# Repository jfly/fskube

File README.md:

fskube 
======

A software modem with a web audio api demo.

* `make` builds the c++ code with clang++. `CXX=g++ make -e` to build with g++.
* `make js` builds fskube.js. Requires emscripten.
* `make jsmin` compresses fskube.js to fskube.min.js. Requires clojure compiler.
* `make check` runs the tests. Requires swig to produce the python wrapper for the c++ code.

* `make serve` starts up a local server

## TODO

* Move off gh-pages branch
* Add android to travis-ci
* Integrate android release with git tags

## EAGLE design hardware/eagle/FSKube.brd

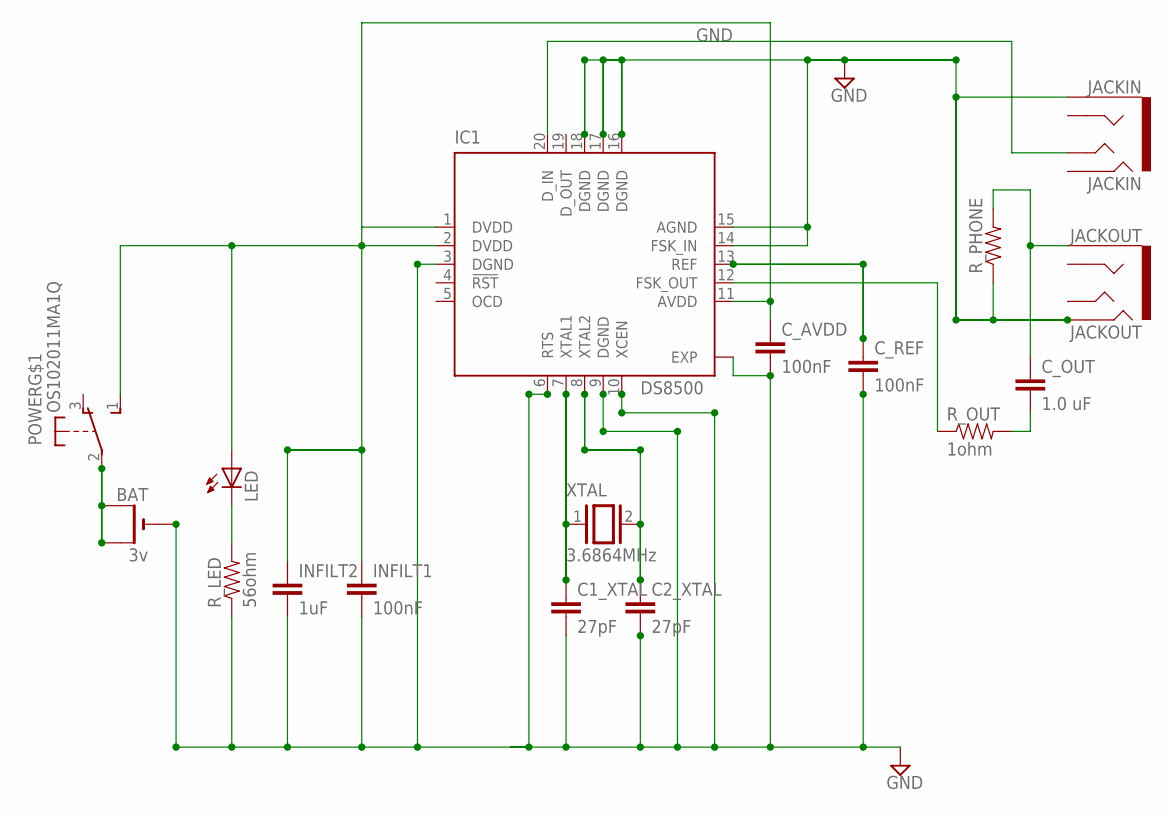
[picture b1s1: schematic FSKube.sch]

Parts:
BAT: 3v; CR1220-THM
C1_XTAL, C2_XTAL: 27pF; C2.5-2
C_AVDD: 100nF; C2.5-2
C_OUT: 1.0 uF; C2.5-2
C_REF: 100nF; C2.5-2
IC1: DS8500; TQFN20-5X5
INFILT1: 100nF; C2.5-2
INFILT2: 1uF; C2.5-2
JACKIN: JACKIN; AUDIO-JACK-TRRS-SMD
JACKOUT: JACKOUT; AUDIO-JACK-TRRS-SMD
LED: LED3MM
POWER: OS102011MA1Q
R_LED: 56ohm; 1/6W-RES
R_OUT: 1ohm; 1/6W-RES
R_PHONE: RESISTORPTH-1/6W; 1/6W-RES
XTAL: 3.6864MHz; QS

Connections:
GND: BAT.-, C1_XTAL.2, C2_XTAL.2, C_AVDD.2, C_REF.2, IC1.3 (DGND), IC1.6 (RTS), IC1.9 (DGND), IC1.10 (XCEN), IC1.14 (FSK_IN), IC1.15 (AGND), IC1.16 (DGND), IC1.17 (DGND), IC1.18 (DGND), IC1.EXP, INFILT1.2, INFILT2.2, JACKIN.EARTH, JACKOUT.RING2, R_LED.1, R_PHONE.1
unnamed: C1_XTAL.1, IC1.7 (XTAL1), XTAL.1
unnamed: C2_XTAL.1, IC1.8 (XTAL2), XTAL.2
unnamed: LED.K (C), R_LED.2
unnamed: IC1.20 (D_IN), JACKIN.TIP
unnamed: BAT.+1 (+), BAT.+2 (+1), POWER.2
unnamed: IC1.12 (FSK_OUT), R_OUT.1
unnamed: C_REF.1, IC1.13 (REF)
unnamed: C_OUT.2, R_OUT.2
unnamed: C_OUT.1, JACKOUT.EARTH, R_PHONE.2
VDD: C_AVDD.1, IC1.1 (DVDD), IC1.2 (DVDD), IC1.11 (AVDD), INFILT1.1, INFILT2.1, LED.A, POWER.1 (S)

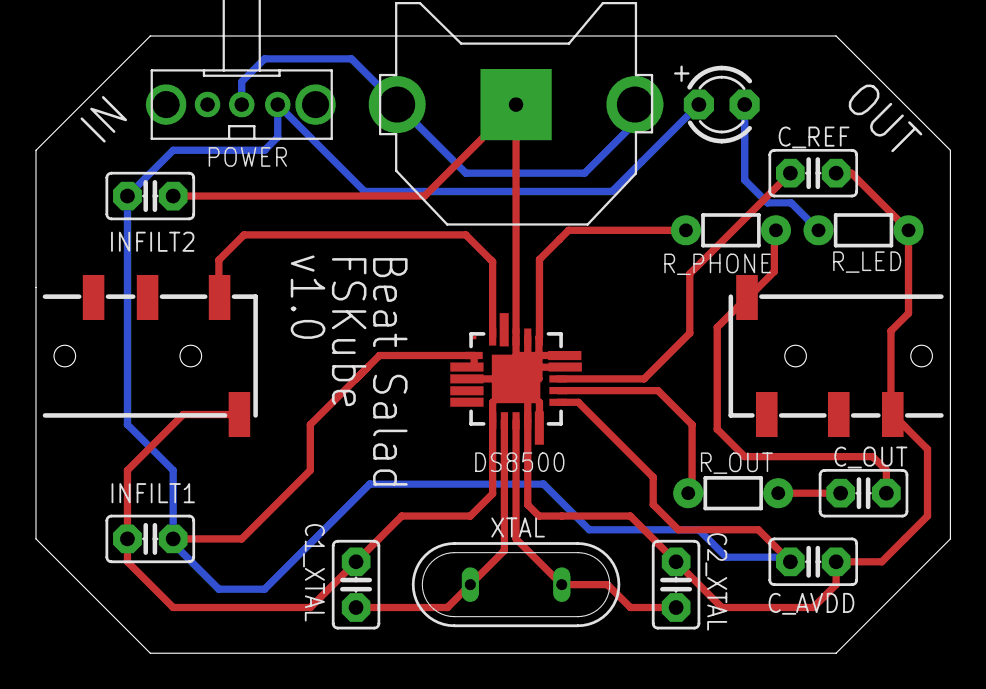
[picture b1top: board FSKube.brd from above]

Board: 2 copper layers, 50.8 x 34.3 mm, 17 parts (0 on the bottom side), 11 nets.

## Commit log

2014-03-09 EVERYTHING. It works, mostly!
2014-03-09 Updated README.
2014-03-09 Shuffled some variables around, increased buffer size so demo works on my Nexus 5.
2014-03-24 Parsing 1200/2200 hz fsk! Seems to work fine.
2014-03-24 Added support for continuous phase fsk-ing. Demodulating doesn't always work =(
2014-05-05 Ported to c++! emscripten and swing, oh my! The current makefile works, but hopefully could be cleaned up.
2014-05-05 Some Makefile cleanup.
2014-05-05 Moved code into a src/ directory. Updated Makefile to generate stuff in the bld/ directory.
2014-05-05 Yayy python unittest!
2014-05-05 ModemRoundtripTest.py now fails =(. I'm pretty sure we have this same bug in the original javascript code, so nothing to worry about =).
2014-05-07 Using emscripten's embind to expose our c++ api to javascript. Unfortunately, embind seems to not support multiple inheritance, so I had to change Sender to be a subclass of Receiver, which seems rea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
2014-05-10 Updated README and Makefile to explain all the different targets we have.
2014-05-10 Ported main.js to use fskube.js! Unfortunately, looks like it's buggy =(.
2014-05-12 Tweaked test to be more python when converting bool to int.
2014-05-12 Now ignoring all text except for "0" and "1" in textboxes.
2014-05-14 Ported example to use c++ modulator/demodulator! Also ported modemtest.js to ModemRoundtripTest.py.
2014-05-14 CLUTTERING HISTORY WITH COMPILED CODE
2014-05-14 fueling my ocd
2014-05-16 Tweaked html demo to use 1200hz and 2200hz, by adding a disgusting amount of padding to our signal.
2014-05-19 Added Rs232or and DeRs232or. Updated index.html to use it! Shuffled test code around a bit.
2014-05-19 Back to using fastcomp!
2014-05-22 Added StackmatSynthesizer and StackmatInterpreter nodes, plus associated test. This required getting fancy with swig typemaps to simulate c pass by value semantics with the StackmatState struct.
2014-05-22 Removing tester.cpp. We can do all our testing in python now thanks to swig.
2014-05-22 Testing!
2014-05-22 Whitelisting gh-pages.
2014-05-22 Adding travis ci icon.
2014-05-22 Adding actual tests
2014-05-22 debuging travis environment
2014-05-22 adding python3-dev to see if we can find some headers
2014-05-22 whoops! order matters
2014-05-22 adding python3.2 for travis ci
2014-05-22 Tweaking test to fail with more information.
2014-05-22 Debugging travis ci failure.
2014-05-22 Gah, everything runs in the same process. Gross.
2014-05-22 hacking logging to be on. disabling tests that produce a lot of spew
2014-05-22 Adding some more debugging info
2014-05-22 everything is falling apart
2014-05-22 Turning off some debugging, commented out most of today's work =(.
2014-05-22 Started pulling common test code into a new FskTest class.
2014-05-22 Logging massively improved! Added swig bindings for it, too, so we can use it in tests as well. This fixes #1.
2014-05-22 Got rid of a duplicate string.
2014-05-22 logging works in javascript too!
2014-05-23 Added getLogLevels() and setLogLevels() functions for controlling logging at runtime. They're available to javascript via getLogLevels() and setLogLevels().
2014-05-23 Separated fskube.h into fsk.h, rs232.h, and stackmat.h. This lets each use their own log handle.
2014-05-23 Renaming DeRs232or and Rs232or to Rs232Synthesizer and Rs232Interpreter.
2014-05-25 Added ui for stackmat signal, right now we're just using JSON, but need to switch to StackmatInterpreter/Synthesizer.
2014-05-28 Stackmat ui now works! Just need to test this out with real hardware =)
2014-05-28 The stackmat flips its data bits!
2014-05-28 speed hack
2014-06-01 Some changes required to compile against the ndk. I'll add something to the makefile and travisci later.
2014-06-01 swig 2.0 (used by travis) doesn't like constexpr.
2014-06-01 Added sample size assertions, fixed wave reading to actually pass in samples in the range -1.0 to 1.0
2014-06-01 Designed a plain old c style api. Right now, it only handles the most the common use case: interpreting an fsk-encoded stackmat signal. I plan to add support for interpreting a digital stackmat signa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
    This is a bit lame, since I'm rather proud of our c++ classes, but
    nothing like swig exists for javascript and java's jni. With enough work,
    we could export our c++ OOP api to js and java, but it would require a
    lot of handwritten glue code (see embind.cpp for what this looks like
    for javascript).
    I plan to get rid of embind.cpp (too much hassle to maintain) and use
2014-06-03 Created c-api and stackmat.js to wrap it using webworkers. stackmat.html is a basic demo.
2014-06-03 Added code to detect if the timer is unplugged/off. More polished stackmat.html demo.
2014-06-03 Stackmat.html is now the homepage. Removed leading 0 from minutes.
2014-06-03 Missing field!
2014-06-03 Added gen3 support to the ui. Demodulation doesn't work so well =(
2014-07-23 Fixed bug with computing max and min wave samples.
2014-07-26 Changed fsk.cpp code to be more restrictive about what it accepts as a "half frequency", this looks like it might fix the issues we have with gen3 running at 1220 baud.
2014-07-26 Now checking checksum and crlf for validity.
2014-07-29 I collected the instruments of digital signal processing around me, that I might infuse a spark of being into the lifeless thing that lay at my feet.
    I tweaked the hell out of the digital signal processing code to get gen3
    to work pretty well on my nexus5. gen2 still works great!
2014-07-29 Removing debugging info.
2014-07-31 Committing eagle files
2014-08-16 Added info div with sample rate.
2014-08-25 Adding fskube-android library! The library will be on jcenter soon. There's also a demo app that uses the library.
    Right now, the c++ code has been copied into the android directory. Will need to come up with a better solution. Perhaps tweaking gradle files, or maybe just symlinks.
2014-08-25 Added TODOs to the README
2014-08-31 pixel pushing
2014-08-31 fskube-android now symlinks to c++ source, rather than copying it
2014-09-01 Added Digitizer to interpret "true" stackmat signal that hasn't gone through a modem. capi now tries to interpret the signal as both fsk encoded and pure, and picks whichever one results in stackmat 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
2014-09-01 We release the mic in onPause(), so we should grab it in onResume, *not* onStart
2014-09-01 added comment
2014-09-02 sweet baby jesus
2014-09-03 update android/README with setup directions
2014-09-03 added link to android/README
2014-09-03 barebones inspection functionality also, change build target to 19 because L is a pain
2014-09-03 updated README wrt SDK version
2014-09-04 added background colors to InspectionActivity
2014-09-04 Updated README.md android setup instructions with my experience on a fresh install of Arch Linux.
    Changed build target for winston back to 20 because I didn't want to install any 19 stuff if I could avoid it.
2014-09-05 updated according to Jeremy's comments
    also, changed SDK target level to 8
2014-09-06 deleted winston (now wingman) from this project BYE
2014-09-13 released 0.0.2!
2014-09-15 Added extrapolation of the last received stackmat signal. Released fskube-android 0.0.4.
2014-09-15 adding -ltr to compile to hopefully make travis-ci happy.
2014-09-15 loosely following advice from http://stackoverflow.com/a/17189535/1739415
2014-09-21 added python3.4m to include path
2014-10-12 We now ignore signals with bad checksums.
2014-10-12 bumping version number
2014-10-12 YES CHECKSUMS
2014-10-12 bumping version to 0.0.6
2014-10-12 Adding isOn and isRunning methods to java api
2014-10-12 whoops, forgot to update header file. bumping to 0.0.8
2017-08-06 Whoops http vs https.

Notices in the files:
parts and their libraries:
SparkFun-Connectors: Licensing: Creative Commons ShareAlike 4.0 International - https://creativecommons.org/licenses/by-sa/4.0
